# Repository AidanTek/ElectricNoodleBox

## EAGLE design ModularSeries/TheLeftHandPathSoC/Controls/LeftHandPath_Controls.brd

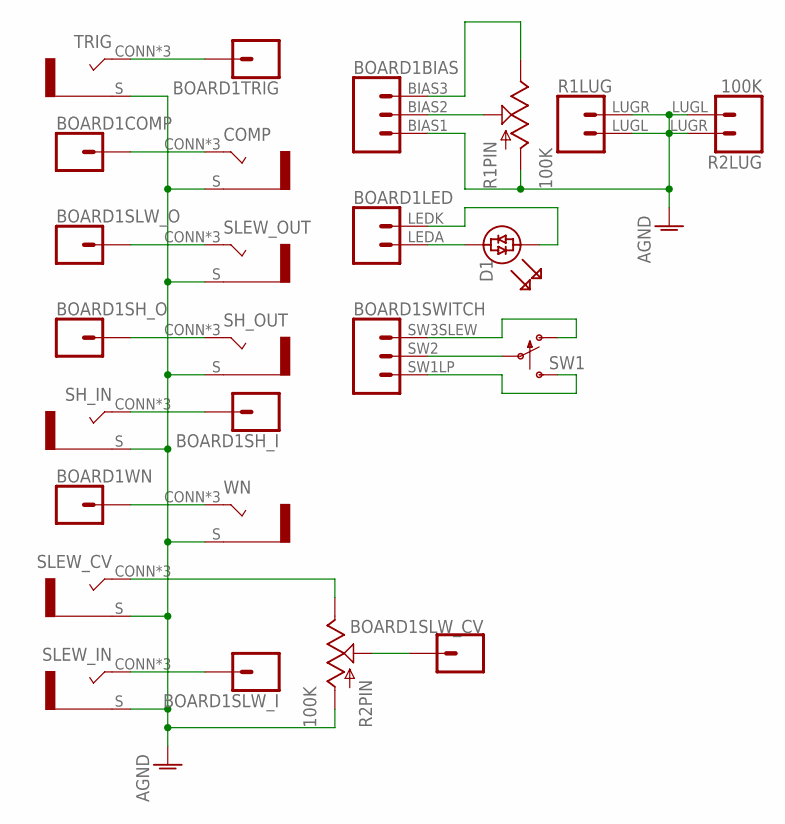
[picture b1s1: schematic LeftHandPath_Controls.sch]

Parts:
BOARD1: TLHPFOC_LINK; TLHPFOC
COMP: COMBI-JACKCINCHNANA; NEWCOMBOJACK_PANEL
D1: 5MM_BICOLOUR_LED; LED5MM
R1, R2: 100K; ALPHA_RV09_9MMPOT
SH_IN: COMBI-JACKCINCHNANA; NEWCOMBOJACK_PANEL
SH_OUT: COMBI-JACKCINCHNANA; NEWCOMBOJACK_PANEL
SLEW_CV: COMBI-JACKCINCHNANA; NEWCOMBOJACK_PANEL
SLEW_IN: COMBI-JACKCINCHNANA; NEWCOMBOJACK_PANEL
SLEW_OUT: COMBI-JACKCINCHNANA; NEWCOMBOJACK_PANEL
SW1: SPDT_SWITCHDW1; MICRODPDT-DW1
TRIG: COMBI-JACKCINCHNANA; NEWCOMBOJACK_PANEL
WN: COMBI-JACKCINCHNANA; NEWCOMBOJACK_PANEL

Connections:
AGND: BOARD1.BIAS1 (1), COMP.S, R1.C1 (A), R1.LUGL (1), R1.LUGR (2), R2.C1 (A), R2.LUGL (1), R2.LUGR (2), SH_IN.S, SH_OUT.S, SLEW_CV.S, SLEW_IN.S, SLEW_OUT.S, TRIG.S, WN.S
unnamed: BOARD1.TRIG (1), TRIG.CONN (T), TRIG.T1 (T), TRIG.T2 (T)
unnamed: BOARD1.COMP (1), COMP.CONN (T), COMP.T1 (T), COMP.T2 (T)
unnamed: BOARD1.SLW_O (1), SLEW_OUT.CONN (T), SLEW_OUT.T1 (T), SLEW_OUT.T2 (T)
unnamed: BOARD1.SH_O (1), SH_OUT.CONN (T), SH_OUT.T1 (T), SH_OUT.T2 (T)
unnamed: BOARD1.SH_I (1), SH_IN.CONN (T), SH_IN.T1 (T), SH_IN.T2 (T)
unnamed: BOARD1.WN (1), WN.CONN (T), WN.T1 (T), WN.T2 (T)
unnamed: BOARD1.BIAS2 (2), R1.C2 (W)
unnamed: BOARD1.LEDA (1), D1.A (AN)
unnamed: BOARD1.LEDK (2), D1.K (KA)
unnamed: BOARD1.SLW_I (1), SLEW_IN.CONN (T), SLEW_IN.T1 (T), SLEW_IN.T2 (T)
unnamed: R2.C3 (B), SLEW_CV.CONN (T), SLEW_CV.T1 (T), SLEW_CV.T2 (T)
unnamed: BOARD1.BIAS3 (3), R1.C3 (B)
unnamed: BOARD1.SW2 (2), SW1.C2
unnamed: BOARD1.SW3SLEW (3), SW1.C1 (O)
unnamed: BOARD1.SW1LP (1), SW1.C3 (S)
unnamed: BOARD1.SLW_CV (1), R2.C2 (W)

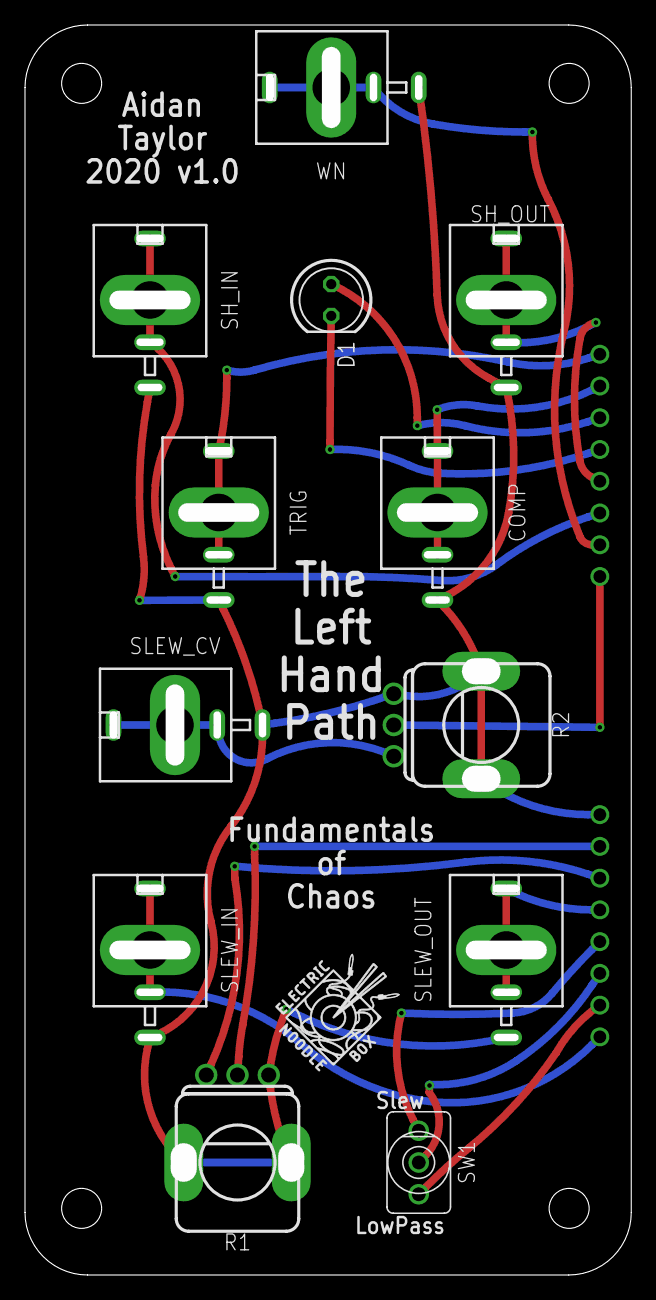
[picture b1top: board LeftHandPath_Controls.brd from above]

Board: 2 copper layers, 48.5 x 100.0 mm, 14 parts (1 on the bottom side), 17 nets.

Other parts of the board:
U$1: LOGO10X10

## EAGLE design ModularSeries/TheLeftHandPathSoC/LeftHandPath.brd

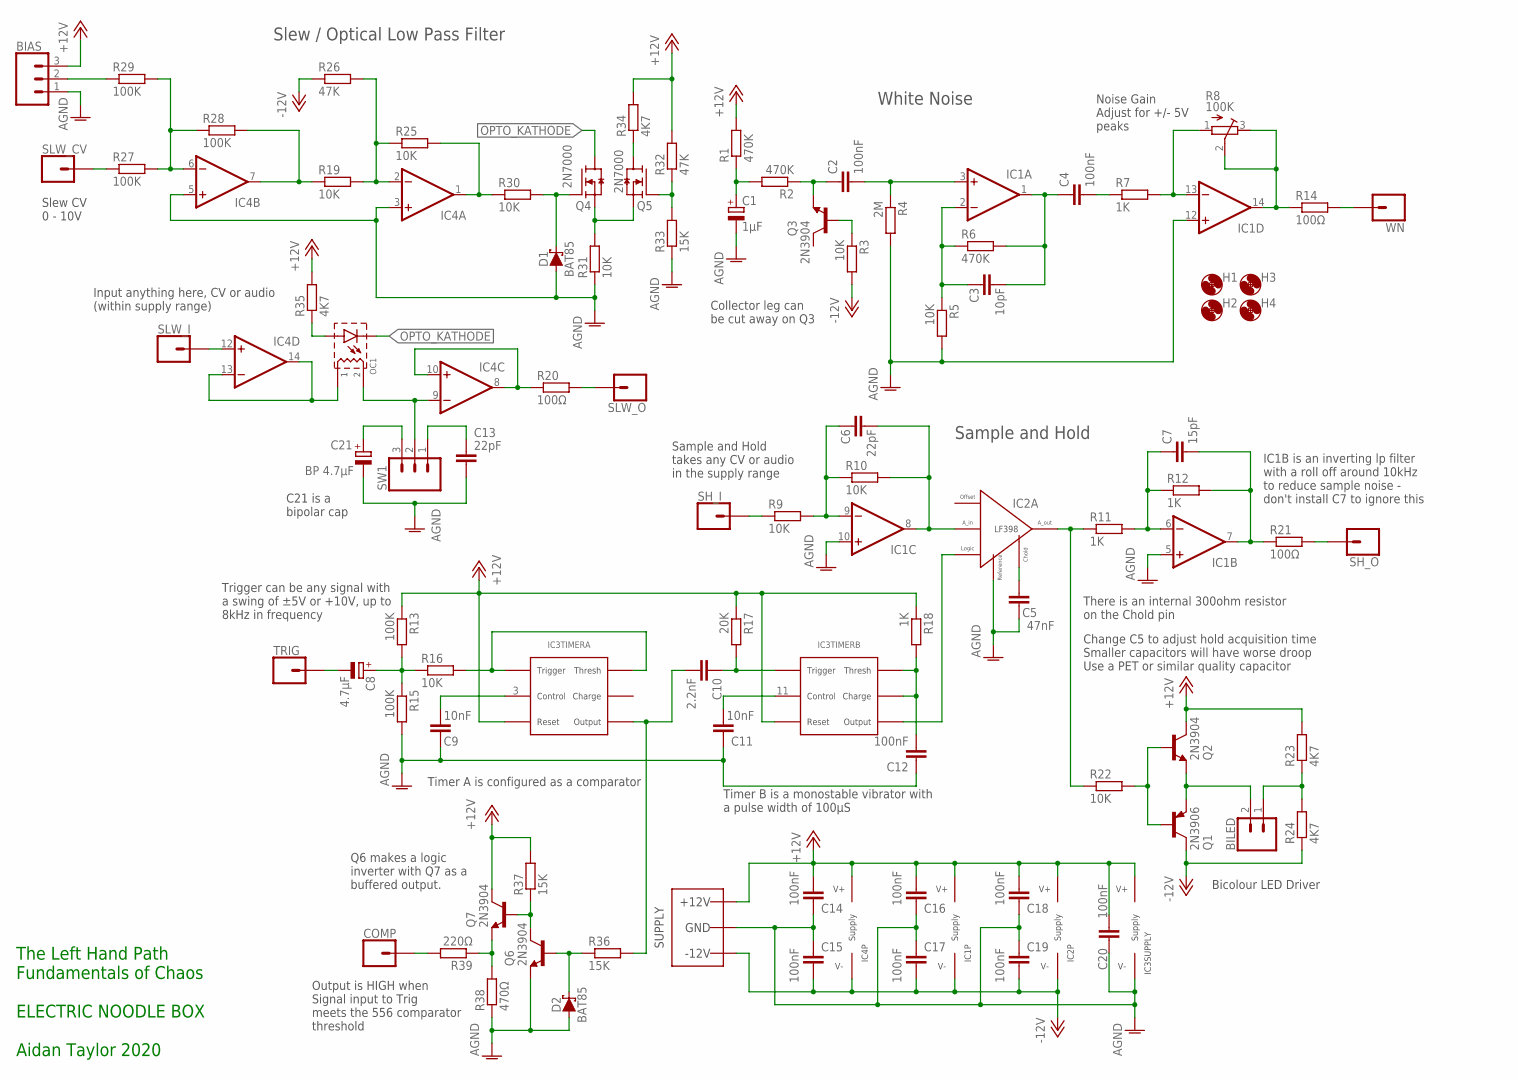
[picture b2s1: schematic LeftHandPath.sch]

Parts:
BIAS: 3XWIREPAD; 1X03
BILED: 2XWIREPAD; 1X02
C1: 1µF; E2-5
C2, C4, C12, C14, C15, C16, C17, C18, C19, C20: 100nF; C050-025X075
C3: 10pF; C050-025X075
C5: 47nF; C050-025X075
C6, C13: 22pF; C050-025X075
C7: 15pF; C050-025X075
C8: 4.7µF; E2-5
C9, C11: 10nF; C050-025X075
C10: 2.2nF; C050-025X075
C21: BP 4.7µF; E2-5
COMP: 1XWIREPAD; 1X01
D1, D2: BAT85; DO35-7
H1, H2, H3, H4: MOUNT-HOLE3.2; 3,2
IC1, IC4: TL0X4DIL; DIL14
IC2: LF398; DIL08
IC3: 556_DUALTIMERDIL14; DIL14
OC1: OPTOCOUPLERSILONEX; SILONEX_OPTOCOUPLER
Q1: 2N3906; TO92
Q2, Q3, Q6, Q7: 2N3904; TO92
Q4, Q5: 2N7000; TO92
R1, R2, R6: 470K; 0207/7
R3, R5, R9, R10, R16, R19, R22, R25, R30, R31: 10K; 0207/7
R4: 2M; 0207/7
R7, R11, R12, R18: 1K; 0207/7
R8: 100K; RTRIM3296W
R13, R15, R27, R28, R29: 100K; 0207/7
R14, R20, R21: 100Ω; 0207/7
R17: 20K; 0207/7
R23, R24, R34, R35: 4K7; 0207/7
R26, R32: 47K; 0207/7
R33, R36, R37: 15K; 0207/7
R38: 470Ω; 0207/7
R39: 220Ω; 0207/7
SH_I: 1XWIREPAD; 1X01
SH_O: 1XWIREPAD; 1X01
SLW_CV: 1XWIREPAD; 1X01
SLW_I: 1XWIREPAD; 1X01
SLW_O: 1XWIREPAD; 1X01
SW1: 3XWIREPAD; 1X03
TRIG: 1XWIREPAD; 1X01
WN: 1XWIREPAD; 1X01
WP1: COMBO_SUPPLY_HEADER; COMBINED_POWER

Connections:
+12V: BIAS.3, C14.2, C16.2, C18.2, C20.2, IC1.4 (V+), IC2.1 (V+), IC3.4 (RESET), IC3.10 (RESET), IC3.14 (V+), IC4.4 (V+), Q2.1 (C), Q7.1 (C), R1.2, R13.1, R17.1, R18.1, R23.2, R32.2, R34.2, R35.2, R37.2, WP1.V+1 (V++), WP1.V+2 (V++), WP1.V+3 (V++)
-12V: C15.1, C17.1, C19.1, IC1.11 (V-), IC2.4 (V-), IC4.11 (V-), Q1.1 (C), R3.2, R24.1, R26.1, WP1.V-1 (V--), WP1.V-2 (V--), WP1.V-3 (V--)
AGND: BIAS.1, C1.-, C5.1, C9.1, C11.1, C12.1, C13.1, C14.1, C15.2, C16.1, C17.2, C18.1, C19.2, C20.1, C21.-, D1.A, D2.A, IC1.5 (+IN), IC1.10 (+IN), IC1.12 (+IN), IC2.7 (REFERENCE), IC3.7 (V-), IC4.3 (+IN), IC4.5 (+IN), Q6.3 (E), R4.2, R5.2, R15.2, R31.1, R33.1, R38.1, WP1.GND1 (AGND), WP1.GND2 (AGND), WP1.GND3 (AGND), WP1.GND4 (AGND), WP1.GND5 (AGND), WP1.GND6 (AGND), WP1.GND7 (AGND), WP1.GND8 (AGND)
unnamed: C1.+, R1.1, R2.2
unnamed: C2.1, Q3.3 (E), R2.1
unnamed: Q3.2 (B), R3.1
unnamed: C2.2, IC1.3 (+IN), R4.1
unnamed: C3.1, IC1.2 (-IN), R5.1, R6.1
unnamed: C3.2, C4.1, IC1.1 (OUT), R6.2
unnamed: C4.2, R7.1
unnamed: IC1.13 (-IN), R7.2, R8.1 (A)
unnamed: IC1.14 (OUT), R8.2 (S), R8.3 (E), R14.1
unnamed: C6.1, IC1.9 (-IN), R9.2, R10.1
unnamed: C6.2, IC1.8 (OUT), IC2.3 (ANALOG_IN), R10.2
unnamed: C5.2, IC2.6 (CH)
unnamed: IC2.5 (ANALOG_OUT), R11.1, R22.1
unnamed: C7.1, IC1.6 (-IN), R11.2, R12.1
unnamed: C7.2, IC1.7 (OUT), R12.2, R21.1
unnamed: R9.1, SH_I.1
unnamed: C10.2, IC3.5 (OUTPUT), R36.2
unnamed: C8.+, R13.2, R15.1, R16.1
unnamed: IC3.2 (THRESHOLD), IC3.6 (TRIGGER), R16.2
unnamed: R14.2, WN.1
unnamed: C9.2, IC3.3 (CONT)
unnamed: C10.1, IC3.8 (TRIGGER), R17.2
unnamed: C11.2, IC3.11 (CONT)
unnamed: C12.2, IC3.12 (THRESHOLD), IC3.13 (DISCHARGE), R18.2
unnamed: IC2.8 (LOGIC), IC3.9 (OUTPUT)
unnamed: C8.-, TRIG.1
unnamed: IC4.12 (+IN), SLW_I.1
unnamed: IC4.13 (-IN), IC4.14 (OUT), OC1.1 (R1)
unnamed: IC4.7 (OUT), R19.1, R28.2
unnamed: IC4.9 (-IN), OC1.2 (R2), SW1.2
unnamed: IC4.8 (OUT), IC4.10 (+IN), R20.1
unnamed: R20.2, SLW_O.1
unnamed: R21.2, SH_O.1
unnamed: Q1.2 (B), Q2.2 (B), R22.2
unnamed: BILED.2, Q1.3 (E), Q2.3 (E)
unnamed: BILED.1, R23.1, R24.2
unnamed: IC4.2 (-IN), R19.2, R25.1, R26.2
unnamed: IC4.6 (-IN), R27.2, R28.1, R29.2
unnamed: IC4.1 (OUT), R25.2, R30.1
unnamed: D1.C, Q4.2 (G), R30.2
unnamed: Q4.1 (S), Q5.1 (S), R31.2
unnamed: C21.+, SW1.3
unnamed: Q5.2 (G), R32.1, R33.2
unnamed: Q5.3 (D), R34.1
unnamed: OC1.A, R35.1
unnamed: C13.2, SW1.1
unnamed: R27.1, SLW_CV.1
unnamed: BIAS.2, R29.1
unnamed: Q6.1 (C), Q7.2 (B), R37.1
unnamed: Q7.3 (E), R38.2, R39.1
unnamed: COMP.1, R39.2
unnamed: D2.C, Q6.2 (B), R36.1
OPTO_KATHODE: OC1.K, Q4.3 (D)

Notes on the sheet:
There is an internal 300ohm resistor on the Chold pin
Collector leg can be cut away on Q3
Noise Gain Adjust for +/- 5V peaks
Change C5 to adjust hold acquisition time Smaller capacitors will have worse droop Use a PET or similar quality capacitor
Timer A is configured as a comparator
Timer B is a monostable vibrator with a pulse width of 100µS
Trigger can be any signal with a swing of ±5V or +10V, up to 8kHz in frequency
IC1B is an inverting lp filter with a roll off around 10kHz to reduce sample noise - don't install C7 to ignore this
White Noise
Slew / Optical Low Pass Filter
Sample and Hold
Bicolour LED Driver
C21 is a bipolar cap
Q6 makes a logic inverter with Q7 as a buffered output.
Output is HIGH when Signal input to Trig meets the 556 comparator threshold
Slew CV 0 - 10V
Input anything here, CV or audio (within supply range)
Sample and Hold takes any CV or audio in the supply range
The Left Hand Path Fundamentals of Chaos ELECTRIC NOODLE BOX Aidan Taylor 2020

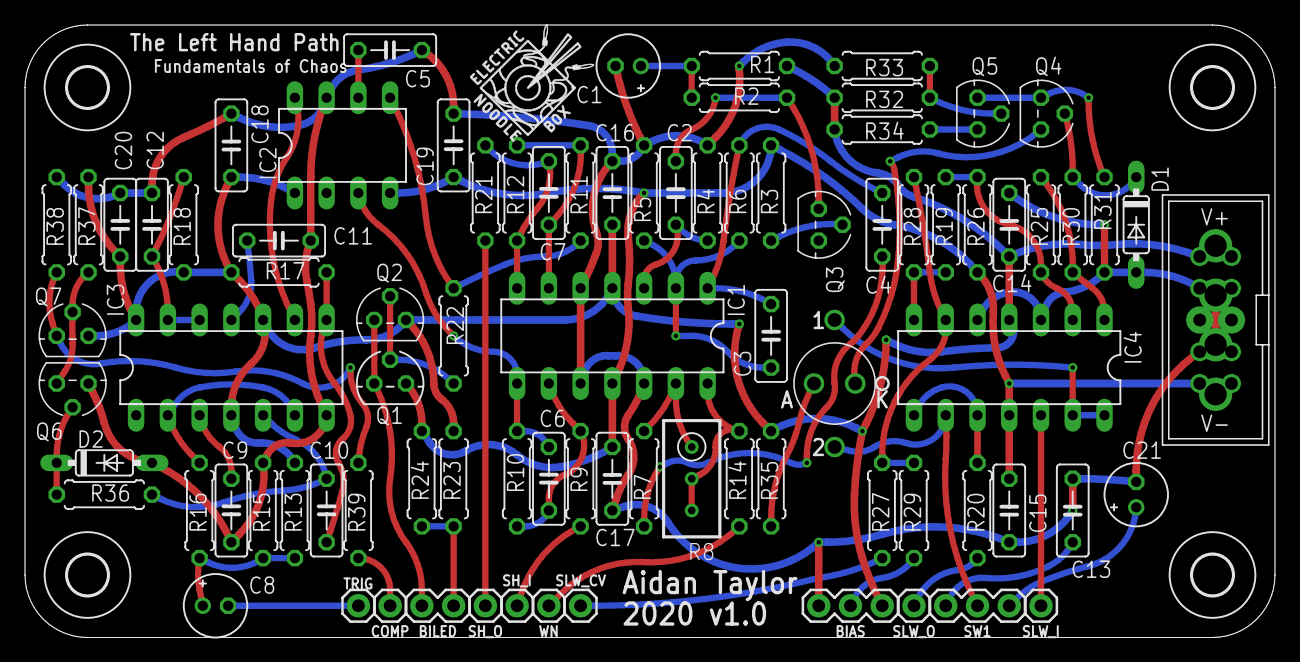
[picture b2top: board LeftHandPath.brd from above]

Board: 2 copper layers, 100.0 x 49.0 mm, 91 parts (0 on the bottom side), 56 nets.

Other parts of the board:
U$1: LOGO10X10

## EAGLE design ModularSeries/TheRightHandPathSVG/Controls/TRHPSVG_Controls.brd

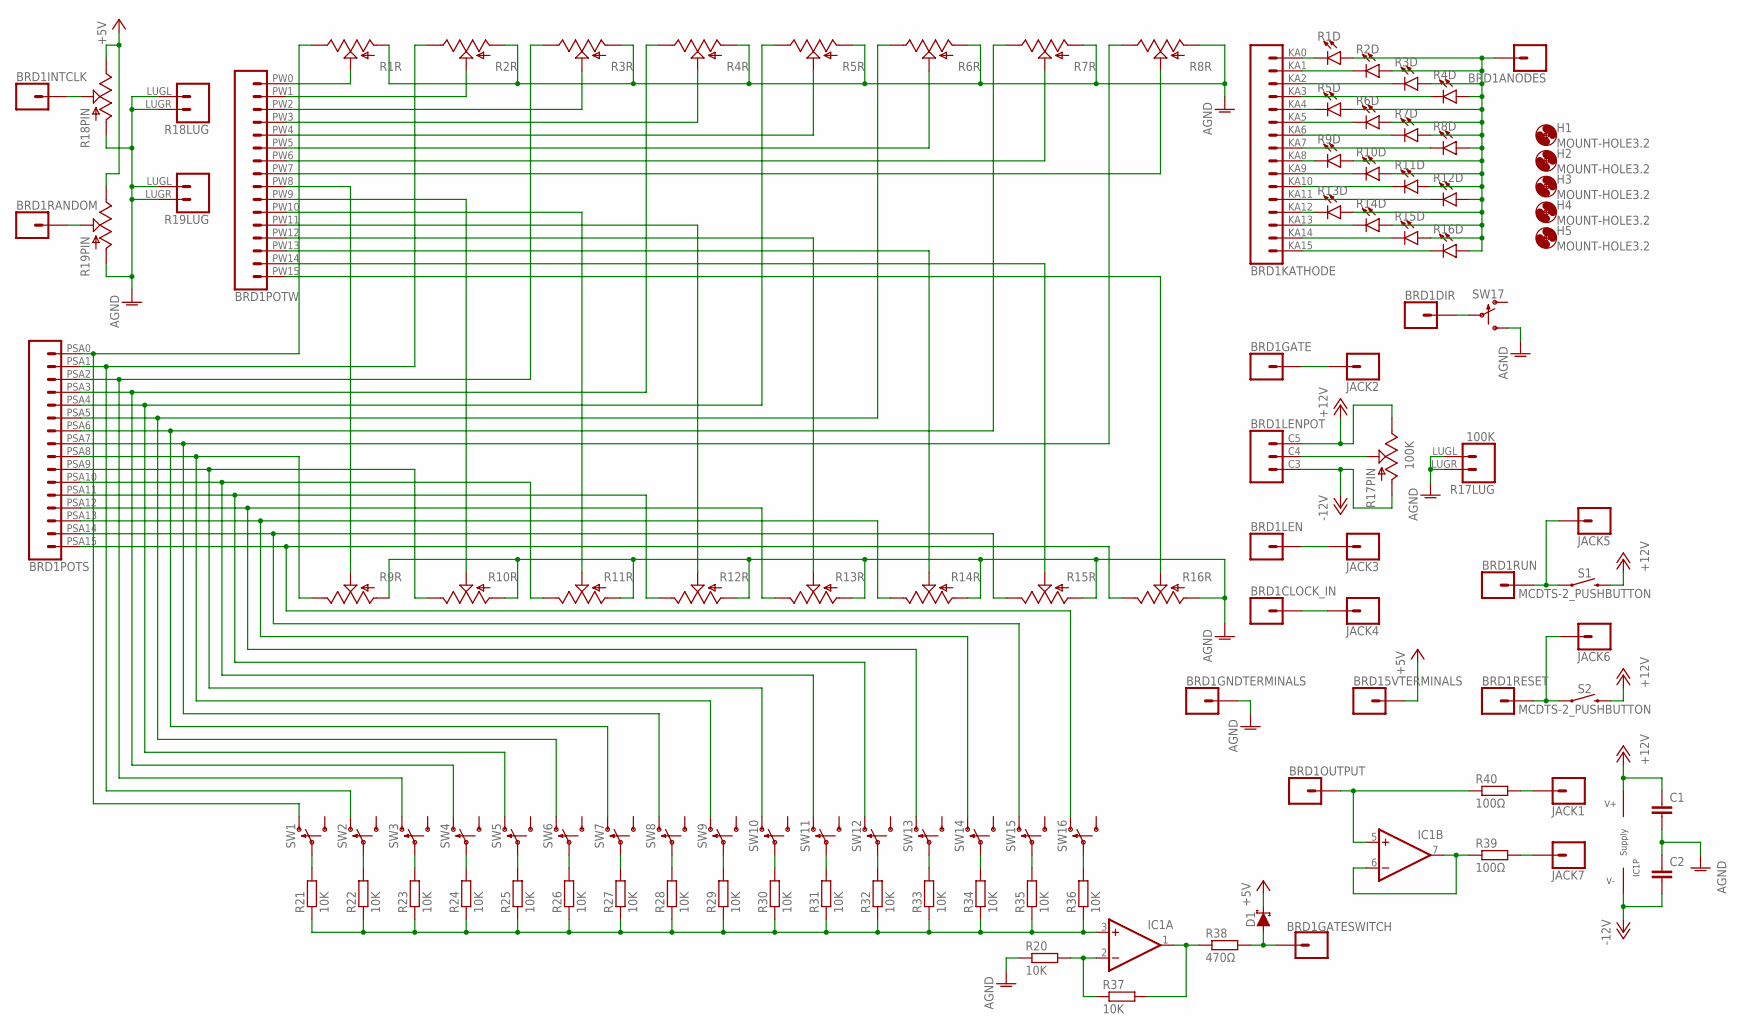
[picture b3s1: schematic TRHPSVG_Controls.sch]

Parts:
BRD1: TRHPSVG_LINK; TRHPSVG
C1, C2: C-EU050-025X075; C050-025X075
D1: SCHOTTKY_DO35; DO35-7
H1, H2, H3, H4, H5: MOUNT-HOLE3.2; 3,2
IC1: TL0X2DIL; DIL08
JACK1, JACK2, JACK3, JACK4, JACK5, JACK6, JACK7: 1XWIREPAD; 1X01
R1, R2, R3, R4, R5, R6, R7, R8, R9, R10, R11, R12, R13, R14, R15, R16: PTL30_SLIDER; LEDSLIDER45MM
R17: 100K; ALPHA_RV09_9MMPOT
R18, R19: POTENTIOMETER; ALPHA_RV09_9MMPOT
R20, R21, R22, R23, R24, R25, R26, R27, R28, R29, R30, R31, R32, R33, R34, R35, R36, R37: 10K; 0207/10
R38: 470Ω; 0207/10
R39, R40: 100Ω; 0207/10
S1, S2: MCDTS-2_PUSHBUTTON
SW1, SW2, SW3, SW4, SW5, SW6, SW7, SW8, SW9, SW10, SW11, SW12, SW13, SW14, SW15, SW16, SW17: SPDT_SWITCHDW1; MICRODPDT-DW1

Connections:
+5V: BRD1.C13 (1), BRD1.C14 (1), BRD1.C15 (1), D1.C, R18.C3 (B), R19.C3 (B)
+12V: BRD1.C5 (3), C1.1, IC1.8 (V+), R17.C3 (B), S1.P$3 (2), S1.P$4 (2), S2.P$3 (2), S2.P$4 (2)
-12V: BRD1.C3 (1), C2.2, IC1.4 (V-), R17.C1 (A)
AGND: BRD1.C16 (1), BRD1.C17 (1), BRD1.C18 (1), BRD1.GNDTA0 (1), BRD1.GNDTA1 (1), BRD1.GNDTA2 (1), BRD1.GNDTA3 (1), BRD1.GNDTA4 (1), BRD1.GNDTA5 (1), BRD1.GNDTA6 (1), BRD1.GNDTA7 (1), BRD1.GNDTA8 (1), BRD1.GNDTA9 (1), BRD1.GNDTA10 (1), BRD1.GNDTA11 (1), BRD1.GNDTA12 (1), BRD1.GNDTA13 (1), BRD1.GNDTA14 (1), BRD1.GNDTA15 (1), C1.2, C2.1, R1.S1 (A), R2.S1 (A), R3.S1 (A), R4.S1 (A), R5.S1 (A), R6.S1 (A), R7.S1 (A), R8.S1 (A), R9.S1 (A), R10.S1 (A), R11.S1 (A), R12.S1 (A), R13.S1 (A), R14.S1 (A), R15.S1 (A), R16.S1 (A), R17.LUGL (1), R17.LUGR (2), R18.C1 (A), R18.LUGL (1), R18.LUGR (2), R19.C1 (A), R19.LUGL (1), R19.LUGR (2), R20.1, SW17.C3 (S)
unnamed: BRD1.PW0 (1), R1.S2 (W)
unnamed: BRD1.PW3 (4), R4.S2 (W)
unnamed: BRD1.PW1 (2), R2.S2 (W)
unnamed: BRD1.PSA0 (1), R1.S3 (B), SW1.C1 (O)
unnamed: BRD1.PSA1 (2), R2.S3 (B), SW2.C1 (O)
unnamed: BRD1.PW2 (3), R3.S2 (W)
unnamed: BRD1.PW4 (5), R5.S2 (W)
unnamed: BRD1.PW5 (6), R6.S2 (W)
unnamed: BRD1.PW6 (7), R7.S2 (W)
unnamed: BRD1.PW7 (8), R8.S2 (W)
unnamed: BRD1.PSA2 (3), R3.S3 (B), SW3.C1 (O)
unnamed: BRD1.PSA3 (4), R4.S3 (B), SW4.C1 (O)
unnamed: BRD1.PSA4 (5), R5.S3 (B), SW5.C1 (O)
unnamed: R36.2, SW16.C2
unnamed: BRD1.PSA6 (7), R7.S3 (B), SW7.C1 (O)
unnamed: BRD1.PSA7 (8), R8.S3 (B), SW8.C1 (O)
unnamed: BRD1.PW8 (9), R9.S2 (W)
unnamed: R21.2, SW1.C2
unnamed: R22.2, SW2.C2
unnamed: BRD1.PW9 (10), R10.S2 (W)
unnamed: R23.2, SW3.C2
unnamed: BRD1.PW10 (11), R11.S2 (W)
unnamed: BRD1.PW11 (12), R12.S2 (W)
unnamed: R24.2, SW4.C2
unnamed: R25.2, SW5.C2
unnamed: BRD1.PW12 (13), R13.S2 (W)
unnamed: BRD1.PW13 (14), R14.S2 (W)
unnamed: BRD1.PSA13 (14), R14.S3 (B), SW14.C1 (O)
unnamed: BRD1.PSA14 (15), R15.S3 (B), SW15.C1 (O)
unnamed: BRD1.PSA15 (16), R16.S3 (B), SW16.C1 (O)
unnamed: BRD1.PW14 (15), R15.S2 (W)
unnamed: BRD1.PW15 (16), R16.S2 (W)
unnamed: BRD1.KA0 (1), R1.SE (C)
unnamed: BRD1.AN0 (1), BRD1.AN1 (1), BRD1.AN2 (1), BRD1.AN3 (1), R1.SB (A), R2.SB (A), R3.SB (A), R4.SB (A), R5.SB (A), R6.SB (A), R7.SB (A), R8.SB (A), R9.SB (A), R10.SB (A), R11.SB (A), R12.SB (A), R13.SB (A), R14.SB (A), R15.SB (A), R16.SB (A)
unnamed: BRD1.KA1 (2), R2.SE (C)
unnamed: BRD1.KA2 (3), R3.SE (C)
unnamed: BRD1.KA3 (4), R4.SE (C)
unnamed: BRD1.KA4 (5), R5.SE (C)
unnamed: BRD1.KA5 (6), R6.SE (C)
unnamed: BRD1.KA6 (7), R7.SE (C)
unnamed: BRD1.KA7 (8), R8.SE (C)
unnamed: BRD1.KA8 (9), R9.SE (C)
unnamed: BRD1.KA9 (10), R10.SE (C)
unnamed: BRD1.KA10 (11), R11.SE (C)
unnamed: BRD1.KA11 (12), R12.SE (C)
unnamed: BRD1.KA12 (13), R13.SE (C)
unnamed: BRD1.KA13 (14), R14.SE (C)
unnamed: BRD1.KA14 (15), R15.SE (C)
unnamed: BRD1.KA15 (16), R16.SE (C)
unnamed: BRD1.C2 (1), JACK3.1
unnamed: BRD1.C6 (1), JACK4.1
unnamed: BRD1.C0 (1), IC1.5 (+IN), R40.1
unnamed: BRD1.C1 (1), JACK2.1
unnamed: BRD1.C11 (1), SW17.C2
unnamed: BRD1.C4 (2), R17.C2 (W)
unnamed: BRD1.PSA5 (6), R6.S3 (B), SW6.C1 (O)
unnamed: BRD1.C9 (1), R18.C2 (W)
unnamed: BRD1.C10 (1), R19.C2 (W)
unnamed: BRD1.C7 (1), JACK5.1, S1.P$1 (1), S1.P$2 (1)
unnamed: BRD1.C8 (1), JACK6.1, S2.P$1 (1), S2.P$2 (1)
unnamed: R26.2, SW6.C2
unnamed: R27.2, SW7.C2
unnamed: R28.2, SW8.C2
unnamed: R29.2, SW9.C2
unnamed: R30.2, SW10.C2
unnamed: R31.2, SW11.C2
unnamed: R32.2, SW12.C2
unnamed: R33.2, SW13.C2
unnamed: BRD1.PSA8 (9), R9.S3 (B), SW9.C1 (O)
unnamed: BRD1.PSA10 (11), R11.S3 (B), SW11.C1 (O)
unnamed: BRD1.PSA9 (10), R10.S3 (B), SW10.C1 (O)
unnamed: BRD1.PSA12 (13), R13.S3 (B), SW13.C1 (O)
unnamed: BRD1.PSA11 (12), R12.S3 (B), SW12.C1 (O)
unnamed: R34.2, SW14.C2
unnamed: R35.2, SW15.C2
unnamed: IC1.3 (+IN), R21.1, R22.1, R23.1, R24.1, R25.1, R26.1, R27.1, R28.1, R29.1, R30.1, R31.1, R32.1, R33.1, R34.1, R35.1, R36.1
unnamed: IC1.2 (-IN), R20.2, R37.1
unnamed: IC1.1 (OUT), R37.2, R38.1
unnamed: BRD1.C12 (1), D1.A, R38.2
unnamed: IC1.6 (-IN), IC1.7 (OUT), R39.1
unnamed: JACK7.1, R39.2
unnamed: JACK1.1, R40.2

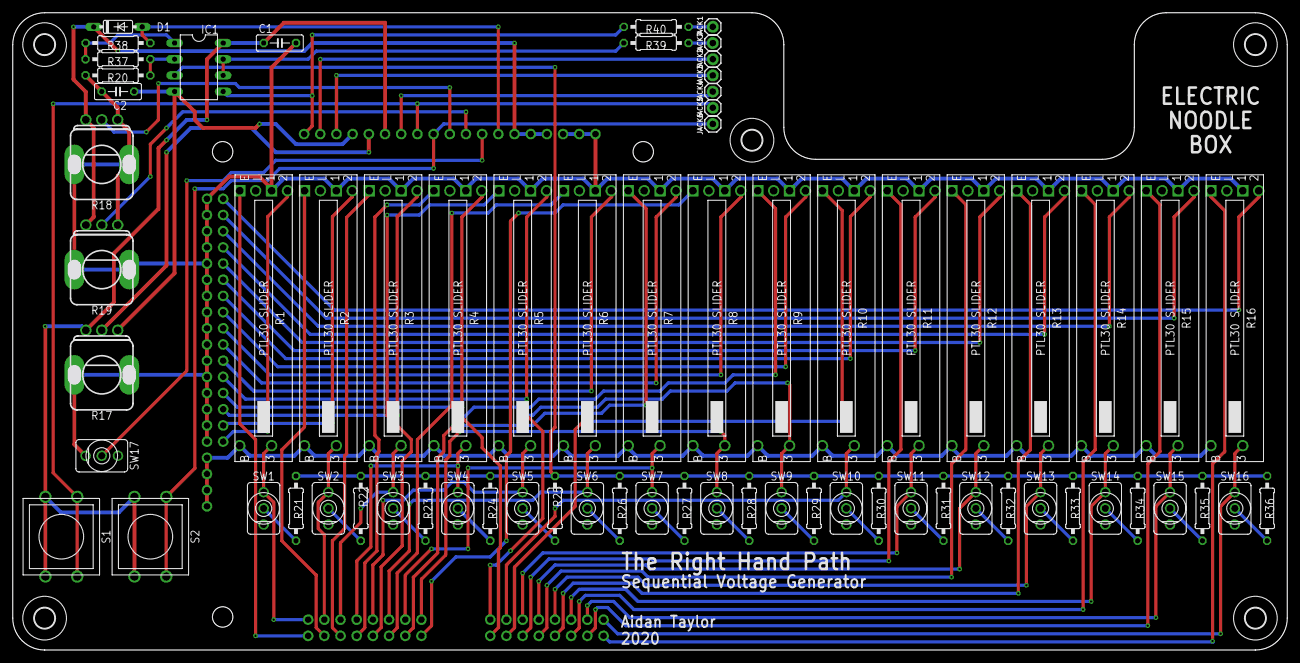
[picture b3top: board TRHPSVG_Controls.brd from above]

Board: 2 copper layers, 200.0 x 100.0 mm, 76 parts (1 on the bottom side), 86 nets.

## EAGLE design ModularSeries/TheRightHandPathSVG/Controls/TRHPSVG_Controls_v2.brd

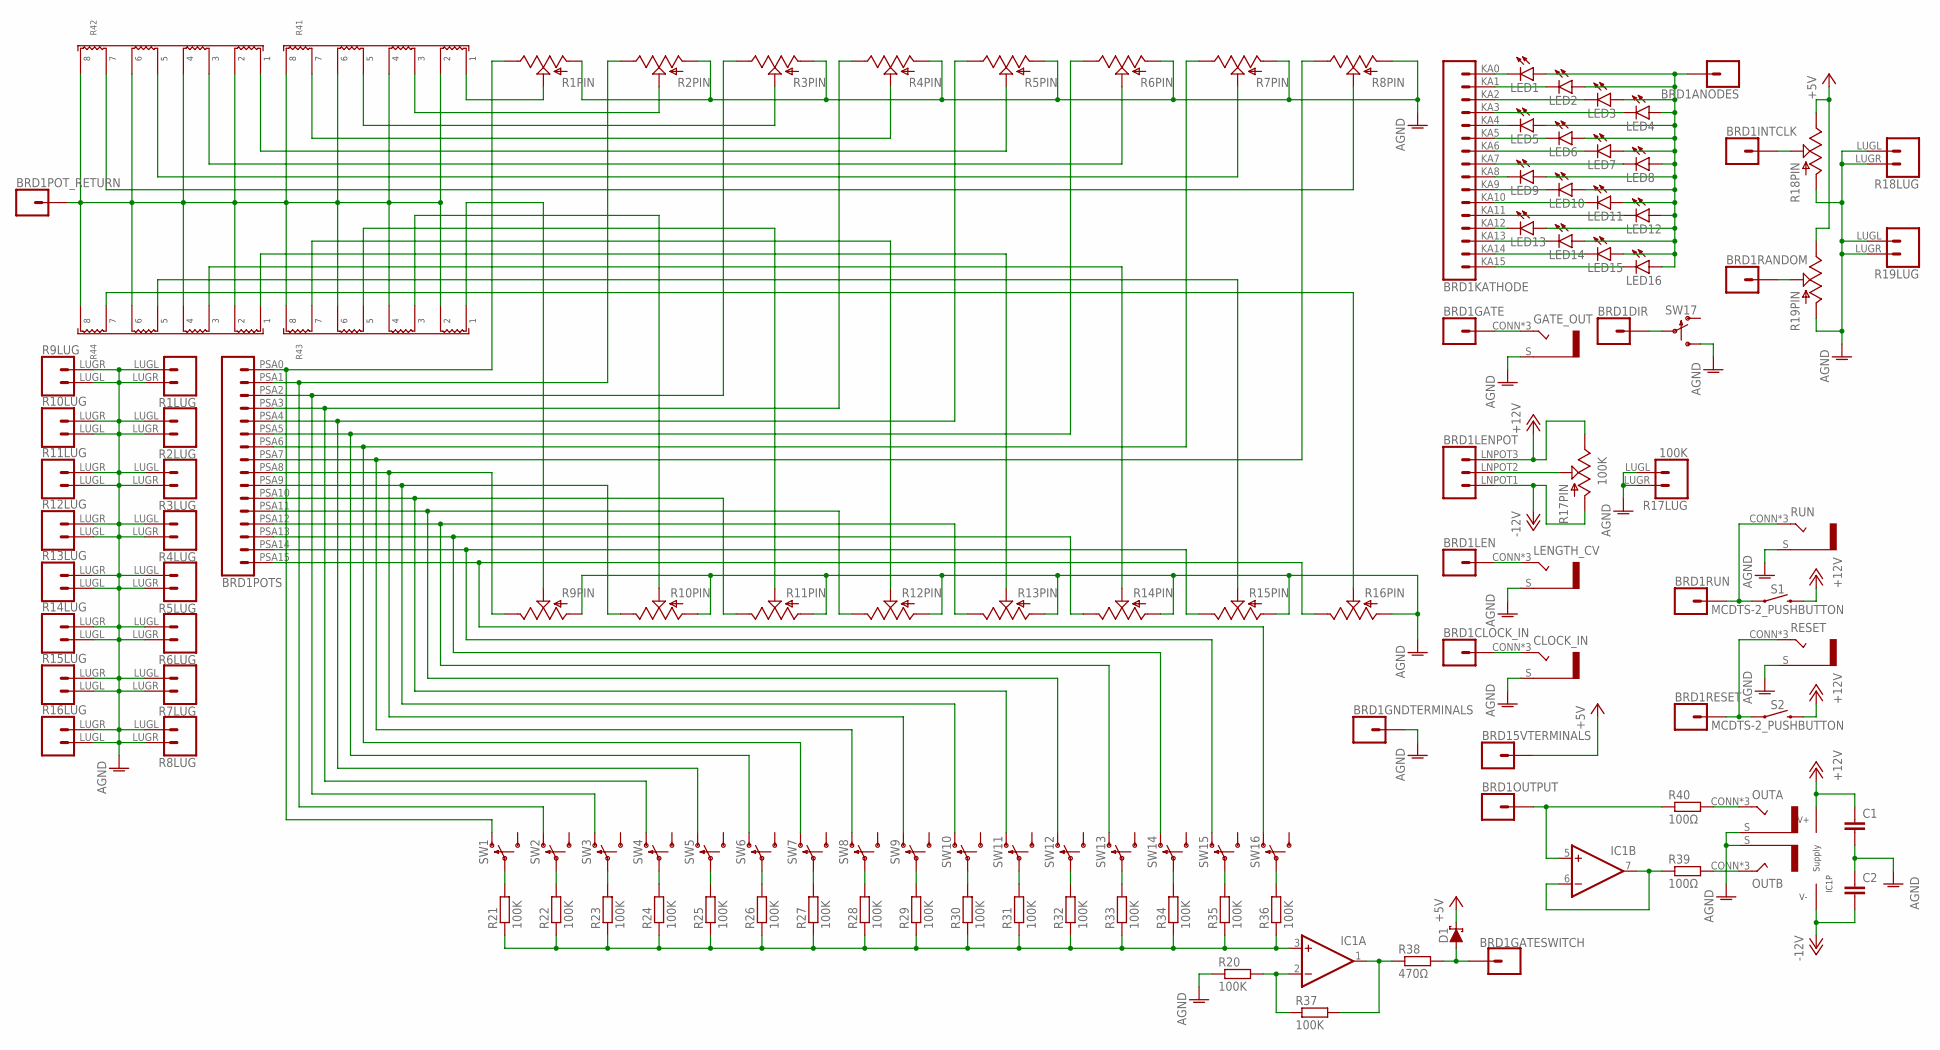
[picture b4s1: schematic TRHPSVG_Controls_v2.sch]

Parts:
BRD1: TRHPSVG_LINK; TRHPSVG
C1, C2: C-EU050-025X075; C050-025X075
CLOCK_IN: COMBI-JACK; COMBOJACK_PANEL
D1: SCHOTTKY_DO35; DO35-7
GATE_OUT: COMBI-JACK; COMBOJACK_PANEL
IC1: TL0X2DIL; DIL08
LED1, LED2, LED3, LED4, LED5, LED6, LED7, LED8, LED9, LED10, LED11, LED12, LED13, LED14, LED15, LED16: LED3MM
LENGTH_CV: COMBI-JACK; COMBOJACK_PANEL
OUTA: COMBI-JACK; COMBOJACK_PANEL
OUTB: COMBI-JACK; COMBOJACK_PANEL
R1, R2, R3, R4, R5, R6, R7, R8, R9, R10, R11, R12, R13, R14, R15, R16, R18, R19: POTENTIOMETER; ALPHA_RV09_9MMPOT
R17: 100K; ALPHA_RV09_9MMPOT
R20, R21, R22, R23, R24, R25, R26, R27, R28, R29, R30, R31, R32, R33, R34, R35, R36, R37: 100K; 0207/10
R38: 470Ω; 0207/10
R39, R40: 100Ω; 0207/10
R41, R42, R43, R44: 4XISO_RESISTOR_NETWORK_2.54; 4_ISO_RES_NET_2.54
RESET: COMBI-JACK; COMBOJACK_PANEL
RUN: COMBI-JACK; COMBOJACK_PANEL
S1, S2: MCDTS-2_PUSHBUTTON
SW1, SW2, SW3, SW4, SW5, SW6, SW7, SW8, SW9, SW10, SW11, SW12, SW13, SW14, SW15, SW16, SW17: SPDT_SWITCHDW1; MICRODPDT-DW1

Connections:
+5V: BRD1.5V1 (1), BRD1.5V2 (1), BRD1.5V3 (1), D1.C, R18.C3 (B), R19.C3 (B)
+12V: BRD1.LNPOT3 (3), C1.1, IC1.8 (V+), R17.C3 (B), S1.P$3 (2), S1.P$4 (2), S2.P$3 (2), S2.P$4 (2)
-12V: BRD1.LNPOT1 (1), C2.2, IC1.4 (V-), R17.C1 (A)
AGND: BRD1.GND1 (1), BRD1.GND2 (1), BRD1.GND3 (1), C1.2, C2.1, CLOCK_IN.S, GATE_OUT.S, LENGTH_CV.S, OUTA.S, OUTB.S, R1.C1 (A), R1.LUGL (1), R1.LUGR (2), R2.C1 (A), R2.LUGL (1), R2.LUGR (2), R3.C1 (A), R3.LUGL (1), R3.LUGR (2), R4.C1 (A), R4.LUGL (1), R4.LUGR (2), R5.C1 (A), R5.LUGL (1), R5.LUGR (2), R6.C1 (A), R6.LUGL (1), R6.LUGR (2), R7.C1 (A), R7.LUGL (1), R7.LUGR (2), R8.C1 (A), R8.LUGL (1), R8.LUGR (2), R9.C1 (A), R9.LUGL (1), R9.LUGR (2), R10.C1 (A), R10.LUGL (1), R10.LUGR (2), R11.C1 (A), R11.LUGL (1), R11.LUGR (2), R12.C1 (A), R12.LUGL (1), R12.LUGR (2), R13.C1 (A), R13.LUGL (1), R13.LUGR (2), R14.C1 (A), R14.LUGL (1), R14.LUGR (2), R15.C1 (A), R15.LUGL (1), R15.LUGR (2), R16.C1 (A), R16.LUGL (1), R16.LUGR (2), R17.LUGL (1), R17.LUGR (2), R18.C1 (A), R18.LUGL (1), R18.LUGR (2), R19.C1 (A), R19.LUGL (1), R19.LUGR (2), R20.1, RESET.S, RUN.S, SW17.C3 (S)
unnamed: R1.C2 (W), R41.P$1
unnamed: R4.C2 (W), R41.P$7
unnamed: R2.C2 (W), R41.P$3
unnamed: BRD1.PSA0 (1), R1.C3 (B), SW1.C1 (O)
unnamed: BRD1.PSA1 (2), R2.C3 (B), SW2.C1 (O)
unnamed: R3.C2 (W), R41.P$5
unnamed: R5.C2 (W), R42.P$1
unnamed: R6.C2 (W), R42.P$3
unnamed: R7.C2 (W), R42.P$5
unnamed: R8.C2 (W), R42.P$7
unnamed: BRD1.PSA2 (3), R3.C3 (B), SW3.C1 (O)
unnamed: BRD1.PSA3 (4), R4.C3 (B), SW4.C1 (O)
unnamed: BRD1.PSA4 (5), R5.C3 (B), SW5.C1 (O)
unnamed: R36.2, SW16.C2
unnamed: BRD1.PSA6 (7), R7.C3 (B), SW7.C1 (O)
unnamed: BRD1.PSA7 (8), R8.C3 (B), SW8.C1 (O)
unnamed: R9.C2 (W), R43.P$1
unnamed: R21.2, SW1.C2
unnamed: R22.2, SW2.C2
unnamed: R10.C2 (W), R43.P$3
unnamed: R23.2, SW3.C2
unnamed: R11.C2 (W), R43.P$5
unnamed: R12.C2 (W), R43.P$7
unnamed: R24.2, SW4.C2
unnamed: R25.2, SW5.C2
unnamed: R13.C2 (W), R44.P$1
unnamed: R14.C2 (W), R44.P$3
unnamed: BRD1.PSA13 (14), R14.C3 (B), SW14.C1 (O)
unnamed: BRD1.PSA14 (15), R15.C3 (B), SW15.C1 (O)
unnamed: BRD1.PSA15 (16), R16.C3 (B), SW16.C1 (O)
unnamed: R15.C2 (W), R44.P$5
unnamed: R16.C2 (W), R44.P$7
unnamed: BRD1.KA0 (1), LED1.K (C)
unnamed: BRD1.AN1 (1), BRD1.AN2 (1), LED1.A, LED2.A, LED3.A, LED4.A, LED5.A, LED6.A, LED7.A, LED8.A, LED9.A, LED10.A, LED11.A, LED12.A, LED13.A, LED14.A, LED15.A, LED16.A
unnamed: BRD1.KA1 (2), LED2.K (C)
unnamed: BRD1.KA2 (3), LED3.K (C)
unnamed: BRD1.KA3 (4), LED4.K (C)
unnamed: BRD1.KA4 (5), LED5.K (C)
unnamed: BRD1.KA5 (6), LED6.K (C)
unnamed: BRD1.KA6 (7), LED7.K (C)
unnamed: BRD1.KA7 (8), LED8.K (C)
unnamed: BRD1.KA8 (9), LED9.K (C)
unnamed: BRD1.KA9 (10), LED10.K (C)
unnamed: BRD1.KA10 (11), LED11.K (C)
unnamed: BRD1.KA11 (12), LED12.K (C)
unnamed: BRD1.KA12 (13), LED13.K (C)
unnamed: BRD1.KA13 (14), LED14.K (C)
unnamed: BRD1.KA14 (15), LED15.K (C)
unnamed: BRD1.KA15 (16), LED16.K (C)
unnamed: BRD1.LENGTH (1), LENGTH_CV.CONN (T), LENGTH_CV.T1 (T), LENGTH_CV.T2 (T)
unnamed: BRD1.CLKIN (1), CLOCK_IN.CONN (T), CLOCK_IN.T1 (T), CLOCK_IN.T2 (T)
unnamed: BRD1.SEQ (1), IC1.5 (+IN), R40.1
unnamed: BRD1.GATE (1), GATE_OUT.CONN (T), GATE_OUT.T1 (T), GATE_OUT.T2 (T)
unnamed: BRD1.DIR (1), SW17.C2
unnamed: BRD1.LNPOT2 (2), R17.C2 (W)
unnamed: BRD1.PSA5 (6), R6.C3 (B), SW6.C1 (O)
unnamed: BRD1.INTC (1), R18.C2 (W)
unnamed: BRD1.RND (1), R19.C2 (W)
unnamed: BRD1.RUN (1), RUN.CONN (T), RUN.T1 (T), RUN.T2 (T), S1.P$1 (1), S1.P$2 (1)
unnamed: BRD1.SRST (1), RESET.CONN (T), RESET.T1 (T), RESET.T2 (T), S2.P$1 (1), S2.P$2 (1)
unnamed: R26.2, SW6.C2
unnamed: R27.2, SW7.C2
unnamed: R28.2, SW8.C2
unnamed: R29.2, SW9.C2
unnamed: R30.2, SW10.C2
unnamed: R31.2, SW11.C2
unnamed: R32.2, SW12.C2
unnamed: R33.2, SW13.C2
unnamed: BRD1.PSA8 (9), R9.C3 (B), SW9.C1 (O)
unnamed: BRD1.PSA10 (11), R11.C3 (B), SW11.C1 (O)
unnamed: BRD1.PSA9 (10), R10.C3 (B), SW10.C1 (O)
unnamed: BRD1.PSA12 (13), R13.C3 (B), SW13.C1 (O)
unnamed: BRD1.PSA11 (12), R12.C3 (B), SW12.C1 (O)
unnamed: R34.2, SW14.C2
unnamed: R35.2, SW15.C2
unnamed: IC1.3 (+IN), R21.1, R22.1, R23.1, R24.1, R25.1, R26.1, R27.1, R28.1, R29.1, R30.1, R31.1, R32.1, R33.1, R34.1, R35.1, R36.1
unnamed: IC1.2 (-IN), R20.2, R37.1
unnamed: IC1.1 (OUT), R37.2, R38.1
unnamed: BRD1.GSW (1), D1.A, R38.2
unnamed: IC1.6 (-IN), IC1.7 (OUT), R39.1
unnamed: OUTB.CONN (T), OUTB.T1 (T), OUTB.T2 (T), R39.2
unnamed: OUTA.CONN (T), OUTA.T1 (T), OUTA.T2 (T), R40.2
unnamed: BRD1.POT-R (1), R41.P$2, R41.P$4, R41.P$6, R41.P$8, R42.P$2, R42.P$4, R42.P$6, R42.P$8, R43.P$2, R43.P$4, R43.P$6, R43.P$8, R44.P$2, R44.P$4, R44.P$6, R44.P$8

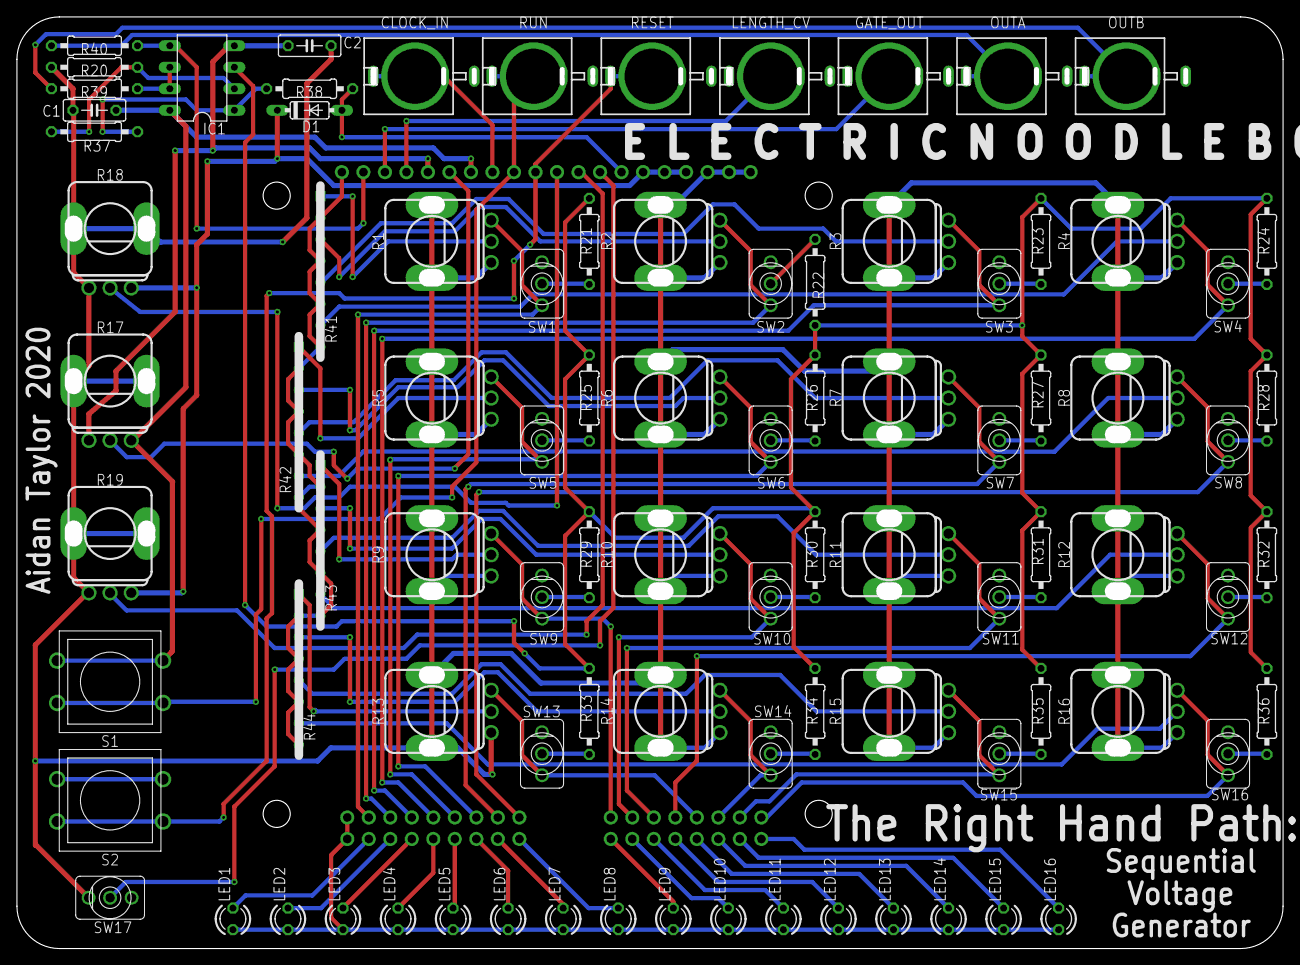
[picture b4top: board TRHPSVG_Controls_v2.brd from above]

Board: 2 copper layers, 149.5 x 110.0 mm, 91 parts (1 on the bottom side), 87 nets.
